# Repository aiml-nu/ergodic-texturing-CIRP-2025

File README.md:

# ergodic-texturing-CIRP-2025
Repository corresponding to our CIRP 2025 paper on using a swarm of robots for large-scale functional texturing.

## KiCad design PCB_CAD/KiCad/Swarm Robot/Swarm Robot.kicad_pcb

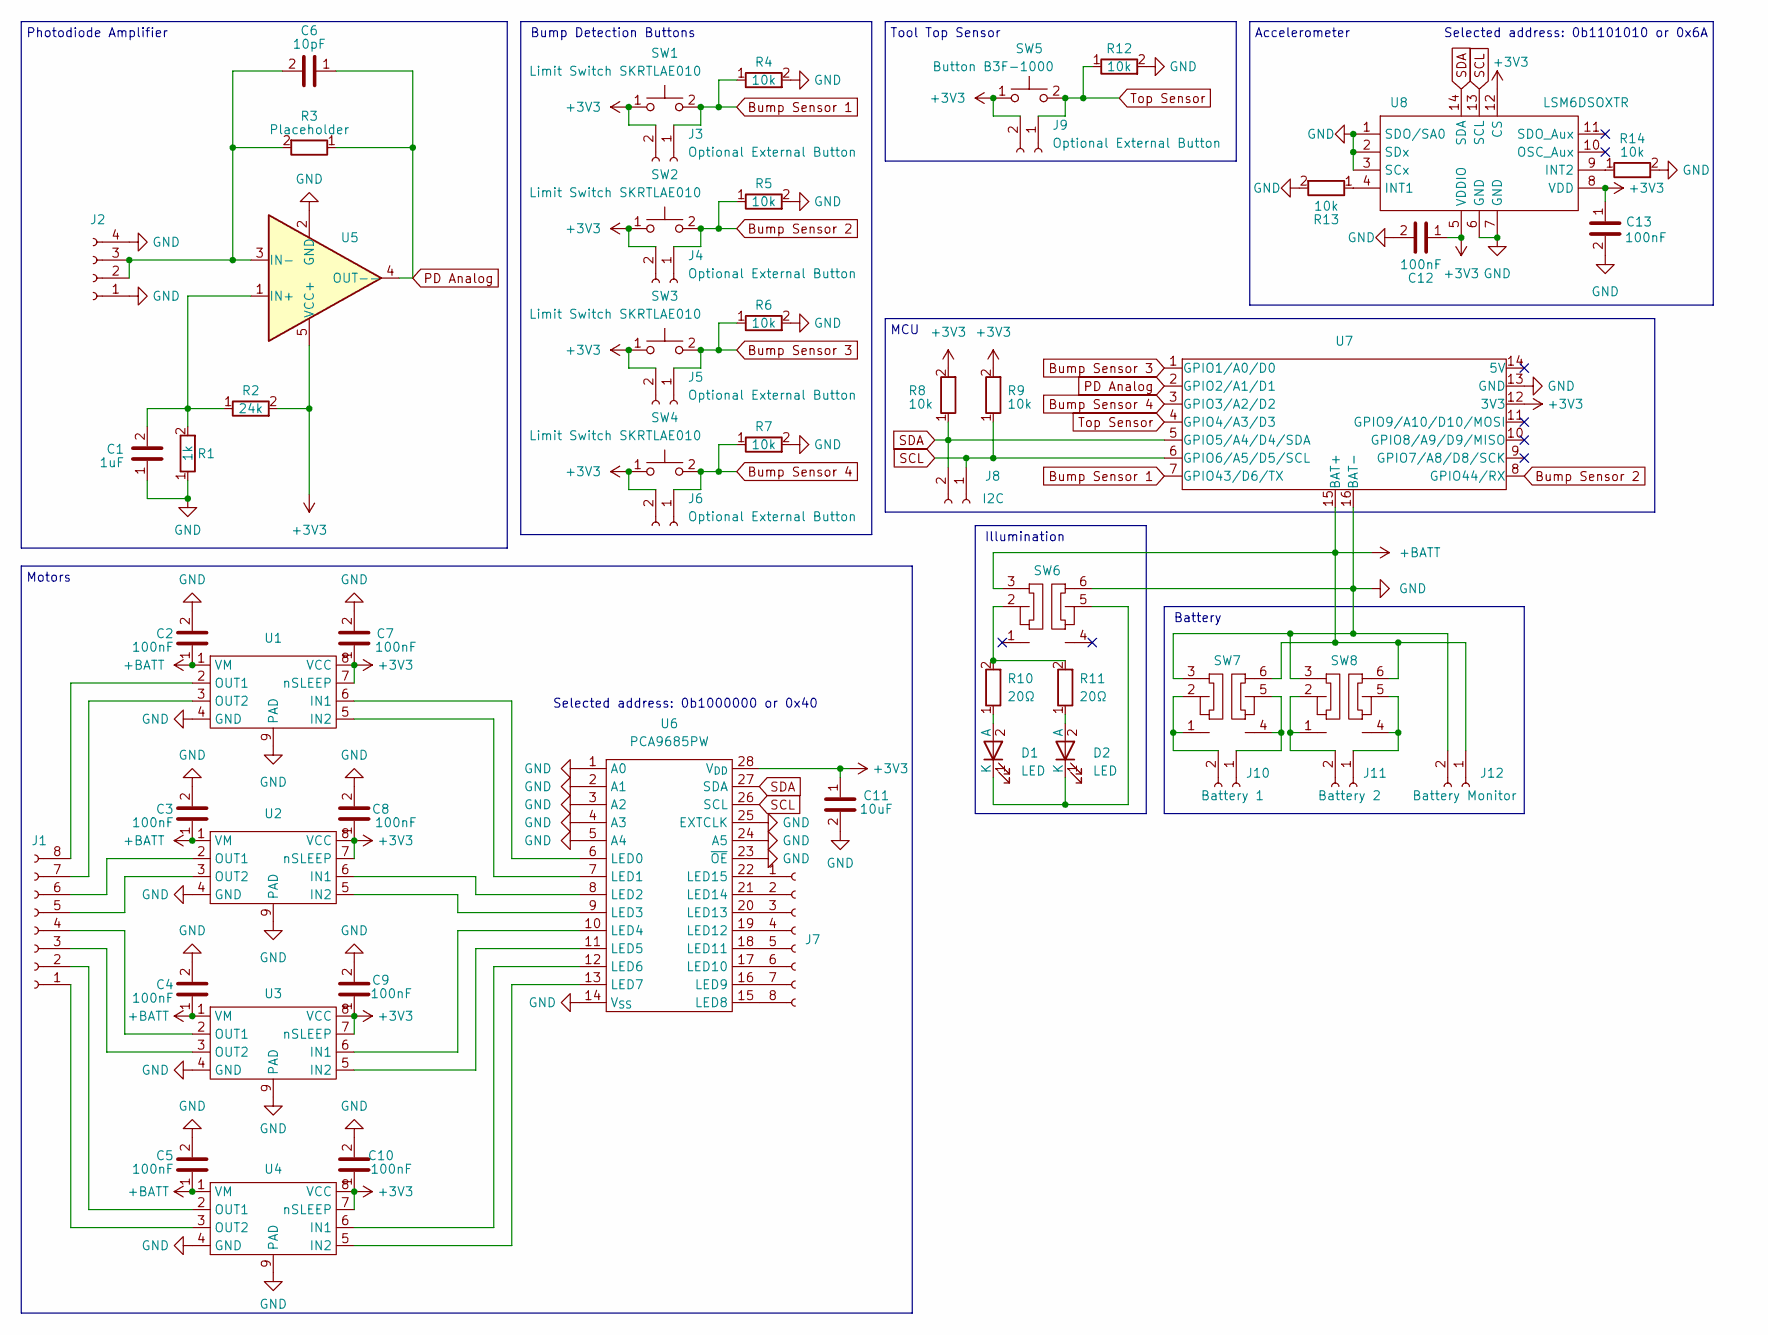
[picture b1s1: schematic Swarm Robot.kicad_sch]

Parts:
C1: 1uF; C_0402_1005Metric; LCSC C52923
C2, C3, C4, C5, C7, C8, C9, C10, C12, C13: 100nF; C_0402_1005Metric; LCSC C307331
C6: 10pF; C_0402_1005Metric; LCSC C32949
C11: 10uF; C_0603_1608Metric; LCSC C96446
D1, D2: LED; LCSC C282149
J1, J7: Conn_01x08_Socket; PinHeader_1x08_P2.54mm_Vertical
J2: Conn_01x04_Socket; PinHeader_1x04_P2.54mm_Vertical
J3, J4, J5, J6, J9: Optional External Button; PinHeader_1x02_P2.54mm_Vertical
J8: I2C; PinHeader_1x02_P2.54mm_Vertical
J10: Battery 1; JST_PH_B2B-PH-SM4-TB_1x02-1MP_P2.00mm_Vertical; LCSC C160352
J11: Battery 2; JST_PH_B2B-PH-SM4-TB_1x02-1MP_P2.00mm_Vertical; LCSC C160352
J12: Battery Monitor; PinHeader_1x02_P2.54mm_Vertical
R1: 1k; R_0402_1005Metric; LCSC C11702
R2: 24k; R_0402_1005Metric; LCSC C25769
R3: Placeholder; R_Axial_DIN0207_L6.3mm_D2.5mm_P10.16mm_Horizontal
R4, R5, R6, R7, R8, R9, R12, R13, R14: 10k; R_0402_1005Metric; LCSC C25744
R10, R11: 20Ω; R_1206_3216Metric; LCSC C431908
SW1, SW2, SW3, SW4: Limit Switch SKRTLAE010; SW_Push_1P1T-MP_NO_Horizontal_Alps_SKRTLAE010; LCSC C110293
SW5: Button B3F-1000; SW_PUSH_6mm
SW6, SW7, SW8: MS-22D28-G020; LCSC C963205
U1, U2, U3, U4: WSON-8-EP(2x2); LCSC C39159
U5: SOT-23-5; LCSC C395459
U6: PCA9685PW; TSSOP-28_4.4x9.7mm_P0.65mm; LCSC C2678753
U7: XIAO_ESP32S3
U8: LSM6DSOXTR; LGA-14_3x2.5mm_P0.5mm_LayoutBorder3x4y; LCSC C481766

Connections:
+3V3: C7.1, C8.1, C9.1, C10.1, C11.1, C12.1, C13.1, J3.2, J4.2, J5.2, J6.2, J9.2, R2.2, R8.2, R9.2, SW1.1, SW2.1, SW3.1, SW4.1, SW5.1, U1.7 (nSLEEP), U1.8 (VCC), U2.7 (nSLEEP), U2.8 (VCC), U3.7 (nSLEEP), U3.8 (VCC), U4.7 (nSLEEP), U4.8 (VCC), U5.5 (VCC+), U6.28 (V_{DD}), U7.12 (3V3), U8.5 (VDDIO), U8.8 (VDD), U8.12 (CS)
+BATT: C2.1, C3.1, C4.1, C5.1, J12.1, SW6.3, SW7.6, SW8.6, U1.1 (VM), U2.1 (VM), U3.1 (VM), U4.1 (VM), U7.15 (BAT+)
Bump Sensor 1: J3.1, R4.1, SW1.2, U7.7 (GPIO43/D6/TX)
Bump Sensor 2: J4.1, R5.1, SW2.2, U7.8 (GPIO44/RX)
Bump Sensor 3: J5.1, R6.1, SW3.2, U7.1 (GPIO1/A0/D0)
Bump Sensor 4: J6.1, R7.1, SW4.2, U7.3 (GPIO3/A2/D2)
GND: C1.1, C2.2, C3.2, C4.2, C5.2, C7.2, C8.2, C9.2, C10.2, C11.2, C12.2, C13.2, J2.1, J2.4, J12.2, R1.1, R4.2, R5.2, R6.2, R7.2, R12.2, R13.2, R14.2, SW6.6, SW7.3, SW8.3, U1.4 (GND), U1.9 (PAD), U2.4 (GND), U2.9 (PAD), U3.4 (GND), U3.9 (PAD), U4.4 (GND), U4.9 (PAD), U5.2 (GND), U6.1 (A0), U6.2 (A1), U6.3 (A2), U6.4 (A3), U6.5 (A4), U6.14 (V_{SS}), U6.23 (~OE), U6.24 (A5), U6.25 (EXTCLK), U7.13 (GND), U7.16 (BAT-), U8.1 (SDO/SA0), U8.2 (SDx), U8.3 (SCx), U8.6 (GND), U8.7 (GND)
unnamed: D1.2 (A), R10.1
unnamed: D1.1 (K), D2.1 (K), SW6.5
unnamed: D2.2 (A), R11.1
unnamed: J10.1, SW7.4, SW7.5
unnamed: J10.2, SW7.1, SW7.2
unnamed: J11.1, SW8.4, SW8.5
unnamed: J11.2, SW8.1, SW8.2
unnamed: R10.2, R11.2, SW6.2
unnamed: U1.6 (IN1), U6.6 (LED0)
unnamed: U1.5 (IN2), U6.7 (LED1)
unnamed: J1.8, U1.2 (OUT1)
unnamed: J1.7, U1.3 (OUT2)
unnamed: U2.6 (IN1), U6.8 (LED2)
unnamed: U2.5 (IN2), U6.9 (LED3)
unnamed: J1.6, U2.2 (OUT1)
unnamed: J1.5, U2.3 (OUT2)
unnamed: U3.6 (IN1), U6.10 (LED4)
unnamed: U3.5 (IN2), U6.11 (LED5)
unnamed: J1.4, U3.2 (OUT1)
unnamed: J1.3, U3.3 (OUT2)
unnamed: U4.6 (IN1), U6.12 (LED6)
unnamed: U4.5 (IN2), U6.13 (LED7)
unnamed: J1.2, U4.2 (OUT1)
unnamed: J1.1, U4.3 (OUT2)
unnamed: C1.2, R1.2, R2.1, U5.1 (IN+)
unnamed: C6.2, J2.2, J2.3, R3.2, U5.3 (IN-)
unnamed: J7.8, U6.15 (LED8)
unnamed: J7.7, U6.16 (LED9)
unnamed: J7.6, U6.17 (LED10)
unnamed: J7.5, U6.18 (LED11)
unnamed: J7.4, U6.19 (LED12)
unnamed: J7.3, U6.20 (LED13)
unnamed: J7.2, U6.21 (LED14)
unnamed: J7.1, U6.22 (LED15)
unnamed: R13.1, U8.4 (INT1)
unnamed: R14.1, U8.9 (INT2)
PD Analog: C6.1, R3.1, U5.4 (OUT--), U7.2 (GPIO2/A1/D1)
SCL: J8.1, R9.1, U6.26 (SCL), U7.6 (GPIO6/A5/D5/SCL), U8.13 (SCL)
SDA: J8.2, R8.1, U6.27 (SDA), U7.5 (GPIO5/A4/D4/SDA), U8.14 (SDA)
Top Sensor: J9.1, R12.1, SW5.2, U7.4 (GPIO4/A3/D3)

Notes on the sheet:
Battery
Accelerometer
Tool Top Sensor
Selected address: 0b1101010 or 0x6A
MCU
Selected address: 0b1000000 or 0x40
Illumination
Photodiode Amplifier
Motors
Bump Detection Buttons

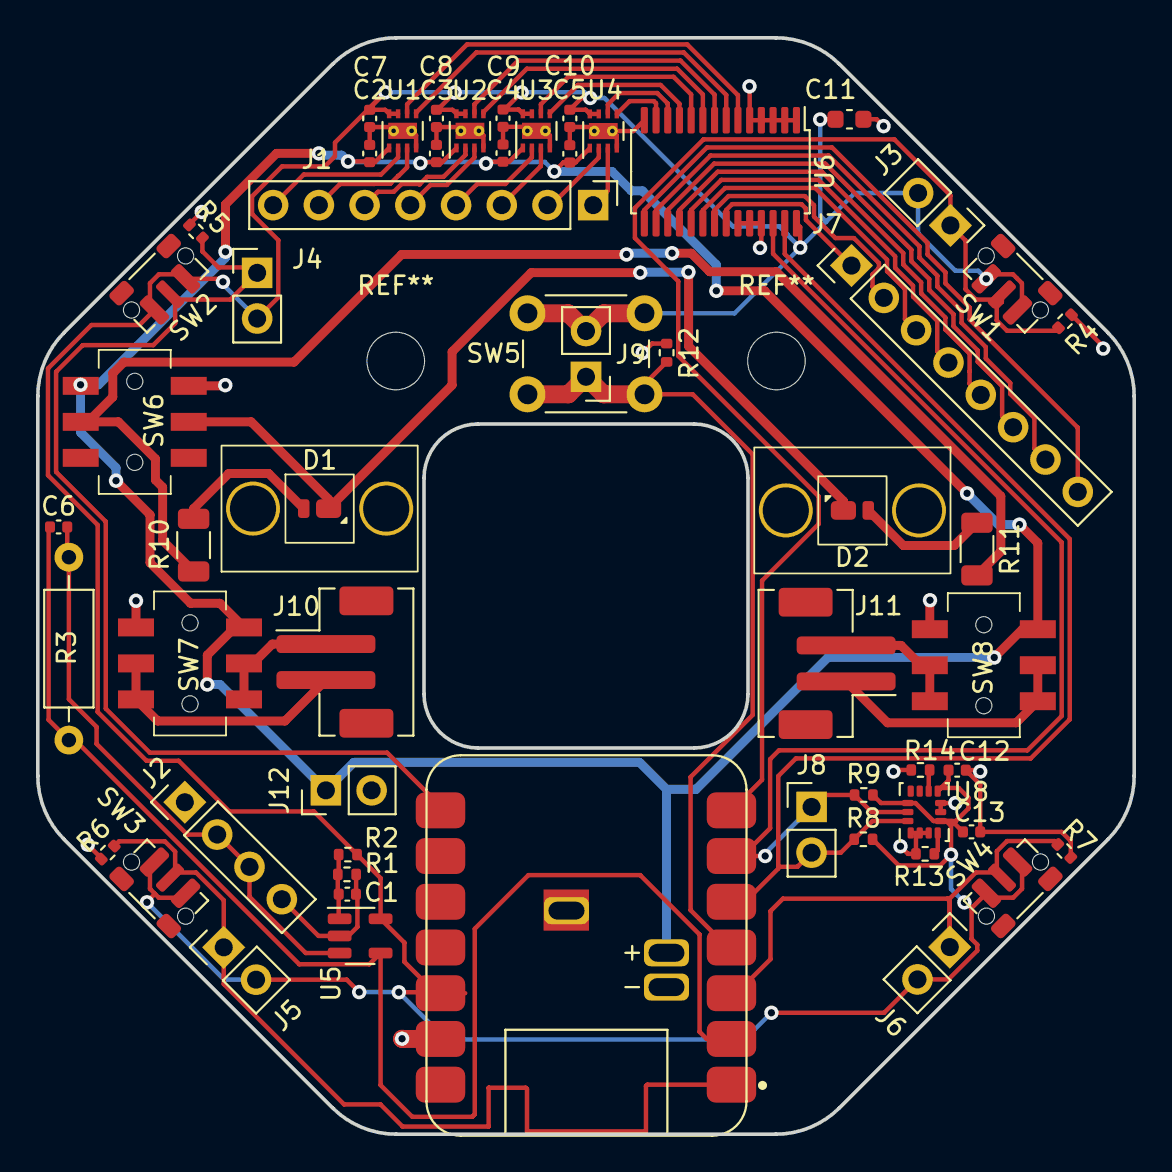
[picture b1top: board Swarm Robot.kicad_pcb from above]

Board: 2 copper layers, 60.9 x 60.9 mm, 57 parts (0 on the bottom side), 47 nets.
